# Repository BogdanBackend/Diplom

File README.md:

Автоматизований портативний комплекс виявлення та аналізу радіосигналів

---

A1:

* [Збірне креслення](pdf/A1/Assem.pdf)
* [Бокс креслення](pdf/A1/Box.pdf)
* [Електрична креслення](pdf/A1/CM5IO.pdf)
* [Експеремент плакат](pdf/A1/A1_experiment.drawio.pdf)
* [Плата плакат](pdf/A1/PCB.pdf)

A4:

* [Записка](pdf/doc.pdf)
* [Захис екрану креслення](pdf/A4/Top.pdf)
* [Захист роз'ємів креслення](pdf/A4/Cover.pdf)
* [Специфікація](pdf/A4/Специфікація.pdf)
* [Звіт плагіату](pdf/A4/Plagiarism.pdf)

---

# __[ЗМІСТ](docs/README.md)__

* [DOCx проміжковий файл розділів](docs/out/doc_dev.docx)

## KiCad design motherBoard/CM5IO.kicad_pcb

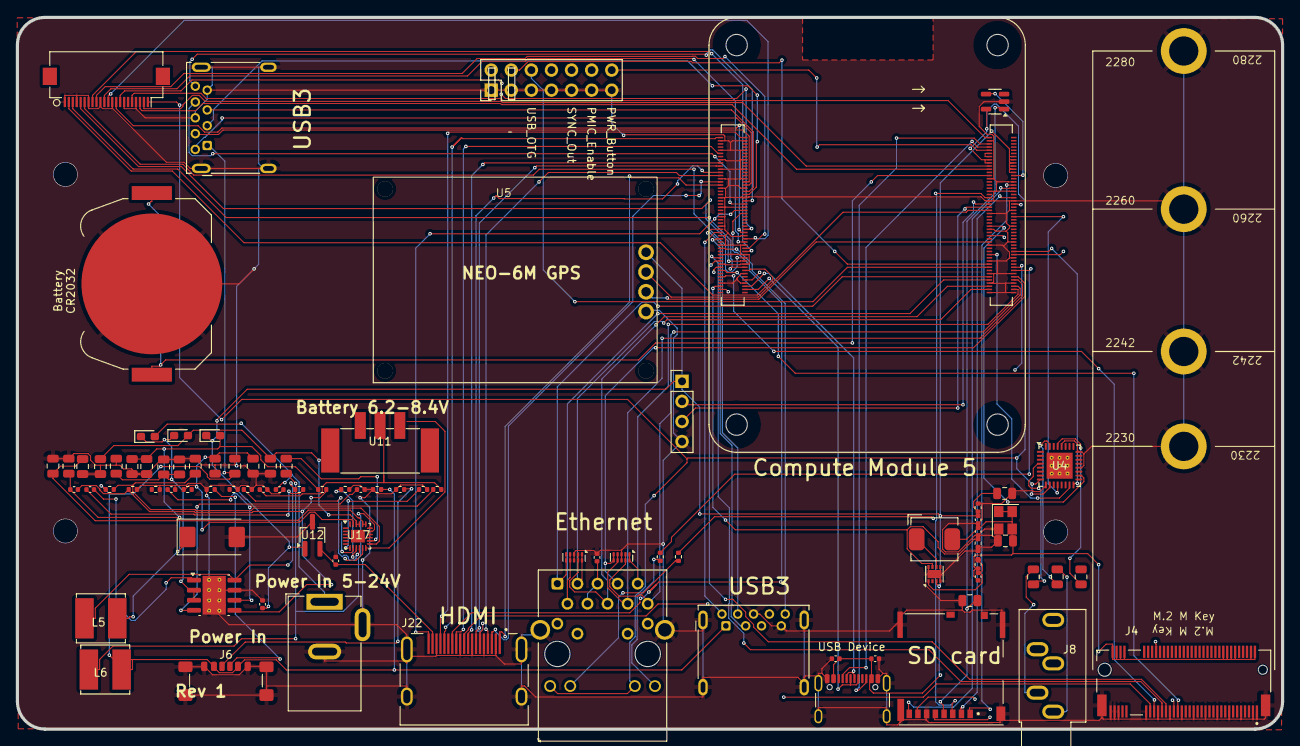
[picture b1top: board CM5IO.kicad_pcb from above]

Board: 4 copper layers, 160.0 x 90.0 mm, 88 parts (0 on the bottom side), 124 nets.

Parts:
BT1: Battery_Cell; BatteryHolder_Keystone_3034_1x20mm
C1, C9, C10, C12, C13, C18, C19, C57, C58: 100n; C_0402_1005Metric
C5, C6, C7, C8, C14, C21, C47, C49, C51, C54, C55, C56, C62, C63, C64, C65, C66, C67: 10u; C_0805_2012Metric
C11: 4.7nF; C_0402_1005Metric
C20: 100uF; CP_EIA-7343-31_Kemet-D
C34, C37, C39: 10u 35v; C_0805_2012Metric
C36: 100n 100v; C_0402_1005Metric
C59, C61: nf; C_0402_1005Metric
C60: 1.2nF; C_0402_1005Metric
D4, D5, D6: D_Zener; D_0603_1608Metric_Pad1.05x0.95mm_HandSolder
J1, J3: USB3_A; USB3_A_Molex_48393-001
J2: Conn_02x07_Odd_Even; PinHeader_2x07_P2.54mm_Vertical
J4: Bus_M.2_Socket_M; M.2 M Key socket
J5: Conn_01x22; Hirose_FH12-22S-0.5SH_1x22-1MP_P0.50mm_Horizontal
J6: USB_C; USB_C_Receptacle_GCT_USB4135-GF-A_6P_TopMnt_Horizontal
J7: Micro_SD_Card_Det; SDCARD_MOLEX_503398-1892
J8: AudioJack; Jack_3.5mm_CUI_SJ1-3535NG_Horizontal
J11: USB_C; USB_C_Receptacle_GCT_USB4105-xx-A_16P_TopMnt_Horizontal
J19: Barrel_Jack; BarrelJack_GCT_DCJ200-10-A_Horizontal
J22: 690-019-298-412; EDAC 690-019-298-412
L1: 2.2uH; L_Bourns_SRP5030CC
L5, L6: SRN6045TA-3R3Y; L_Bourns_SRN6045TA
Module1: ComputeModule5-CM5; Raspberry-Pi-5-Compute-Module
R2, R3: 470R; R_0402_1005Metric
R9, R16, R28: 2.2K 1%; R_0402_1005Metric
R10, R22, R23, R24, R30, R31: 10R; R_0402_1005Metric
R14: 100K; R_0402_1005Metric
R15: 10K 1%; R_0402_1005Metric
R25: 20K 1%; R_0402_1005Metric
R27: 12K 1%; R_0402_1005Metric
R34: 12K; R_0402_1005Metric
R35: 10K; R_0402_1005Metric
R37: 0.5K; R_0402_1005Metric
R38: 1K; R_0402_1005Metric
R39: 18K; R_0402_1005Metric
U1, U2: TPD4EUSB30; USON-10_2.5x1.0mm_P0.5mm
U3: MagJack-A70-112; TRJG0926HENL
U4: WM8960; QFN-32-1EP_5x5mm_P0.5mm_EP3.3x3.3mm_ThermalVias
U5: NEO-6M GPS
U6: Touch; PinHeader_1x04_P2.54mm_Vertical
U7: 32.768KHZ; Crystal_SMD_3225-4Pin_3.2x2.5mm
U8: AP3441SHE-7B; DFN-8-1EP_2x2mm_P0.5mm_EP1.05x1.75mm
U11: BK-18650-PC4; TerminalBlock_Phoenix_PTSM-0,5-3-2,5-V-SMD_1x03-1MP_P2.50mm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
U12: RT9742SNGV; TSOT-23_HandSoldering
U16: AP64501SP-13; SOIC-8-1EP_3.9x4.9mm_P1.27mm_EP2.95x4.9mm_Mask2.71x3.4mm_Th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
U17: IP2326; QFN-24-1EP_3x3mm_P0.4mm_EP1.75x1.6mm
U18: RT9742GGJ5; SOT-23-5

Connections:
/+1.8v: Module1.88 (+1.8v_(Output)), Module1.90 (+1.8v_(Output))
/+3.3v: J5.22, Module1.84 (+3.3v_(Output)), Module1.86 (+3.3v_(Output)), U3.15 (LEDY_A), U3.17 (LEDG_A), U4.8 (DCVDD), U4.10 (DBVDD), U18.5 (IN)
/+5v: C6.1, C9.1, C10.1, C12.1, C18.1, D4.1 (K), J11.A4 (VBUS), J11.A9 (VBUS), J11.B4 (VBUS), J11.B9 (VBUS), Module1.77 (+5v_(Input)), Module1.79 (+5v_(Input)), Module1.81 (+5v_(Input)), Module1.83 (+5v_(Input)), Module1.85 (+5v_(Input)), Module1.87 (+5v_(Input)), R9.2, U5.1 (VCC), U6.1 (VCC), U8.3 (VIN), U12.1 (IN)
/+12v: C34.1, C37.1, C39.1, D5.1 (K), D6.1 (K), U16.2 (VIN), U16.3 (EN)
/CAM_GPIO1: J5.18, Module1.100 (CAM_GPIO1)
/CC1: J11.A5 (CC1), Module1.94 (CC1)
/CC2: J11.B5 (CC2), Module1.96 (CC2)
/DPHY0_C_N: J5.8, Module1.127 (MIPI0_C_N)
/DPHY0_C_P: J5.9, Module1.129 (MIPI0_C_P)
/DPHY0_D0_N: J5.2, Module1.115 (MIPI0_D0_N)
/DPHY0_D0_P: J5.3, Module1.117 (MIPI0_D0_P)
/DPHY0_D1_N: J5.5, Module1.121 (MIPI0_D1_N)
/DPHY0_D1_P: J5.6, Module1.123 (MIPI0_D1_P)
/DPHY0_D2_N: J5.11, Module1.133 (MIPI0_D2_N)
/DPHY0_D2_P: J5.12, Module1.135 (MIPI0_D2_P)
/DPHY0_D3_N: J5.14, Module1.139 (MIPI0_D3_N)
/DPHY0_D3_P: J5.15, Module1.141 (MIPI0_D3_P)
/EEPROM_nWP: J2.4, Module1.20 (EEPROM_nWP)
/ETH_LEDG: Module1.17 (Ethernet_nLED2(3.3v)), R2.2
/ETH_LEDY: Module1.15 (Ethernet_nLED3(3.3v)), R3.2
/FB: C11.2, R15.2, R16.1, U8.1 (FB)
/GPIO2: Module1.58 (GPIO2), U6.2 (SDA)
/GPIO3: Module1.56 (GPIO3), U6.3 (SCL)
/GPIO4: Module1.54 (GPIO4), U5.2 (RX)
/GPIO5: Module1.34 (GPIO5), U5.3 (TX)
/GPIO10: Module1.44 (GPIO10), U4.18 (SDA)
/GPIO11: Module1.38 (GPIO11), U4.17 (SCL)
/GPIO18: Module1.49 (GPIO18), U4.12 (BCLK)
/GPIO19: Module1.26 (GPIO19), U4.15 (ADCLRC/GPIO)
/GPIO20: Module1.27 (GPIO20), U4.16 (ADCDAT)
/GPIO21: Module1.25 (GPIO21), U4.14 (DACDAT)
/HDMI0_CEC: J22.13 (CEC), Module1.151 (HDMI0_CEC)
/HDMI0_CK_N: J22.12 (CK-), Module1.190 (HDMI0_CLK_N)
/HDMI0_CK_P: J22.10 (CK+), Module1.188 (HDMI0_CLK_P)
/HDMI0_D0_N: J22.9 (D0-), Module1.184 (HDMI0_TX0_N)
/HDMI0_D0_P: J22.7 (D0+), Module1.182 (HDMI0_TX0_P)
/HDMI0_D1_N: J22.6 (D1-), Module1.178 (HDMI0_TX1_N)
/HDMI0_D1_P: J22.4 (D1+), Module1.176 (HDMI0_TX1_P)
/HDMI0_D2_N: J22.3 (D2-), Module1.172 (HDMI0_TX2_N)
/HDMI0_D2_P: J22.1 (D2+), Module1.170 (HDMI0_TX2_P)
/HDMI0_HOTPLUG: J22.19 (HPD/HEAC-), Module1.153 (HDMI0_HOTPLUG)
/HDMI0_SCL: J22.15 (SCL), Module1.200 (HDMI0_SCL)
/HDMI0_SDA: J22.16 (SDA), Module1.199 (HDMI0_SDA)
/HDMI_5v: C13.1, J22.18 (+5V), U12.2 (OUT)
/M2_3v3: C11.1, C14.1, C19.1, J4.2 (3.3V), J4.4 (3.3V), J4.12 (3.3V), J4.14 (3.3V), J4.16 (3.3V), J4.18 (3.3V), J4.68 (SUSCLK), J4.70 (3.3V), J4.72 (3.3V), J4.74 (3.3V), L1.2, R15.1, U7.1 (EN), U7.3 (Out), U7.4 (VDD)
/PCIE_CLK_N: J4.53 (REFCLKn), Module1.112 (PCIe_CLK_N)
/PCIE_CLK_P: J4.55 (REFCLKp), Module1.110 (PCIe_CLK_P)
/PCIE_PWR_EN: Module1.106 (PCIE_PWR_EN), R14.1, U8.7 (EN)
/PCIE_RX_N: J4.43 (PETp0), Module1.118 (PCIe_RX_N)
/PCIE_RX_P: J4.41 (PETn0), Module1.116 (PCIe_RX_P)
/PCIE_TX_N: J4.49 (PERp0), Module1.124 (PCIe_TX_N)
/PCIE_TX_P: J4.47 (PERn0), Module1.122 (PCIe_TX_P)
/PCIE_nCLKREQ: J4.52 (~CLKREQ), Module1.102 (PCIe_nCLKREQ)
/PCIE_nRST: J4.50 (~PERST), Module1.109 (PCIe_nRST)
/PCIE_nWAKE: J4.54 (~PEWAKE), Module1.104 (PCIE_nWAKE)
/PWR_BUT: J2.14, Module1.92 (PWR_BUT)
/SCL0: J5.20, Module1.80 (SCL0)
/SDA0: J5.21, Module1.82 (SDA0)
/SD_CLK: J7.5 (CLK), Module1.57 (SD_CLK)
/SD_CMD: J7.3 (CMD), Module1.62 (SD_CMD)
/SD_DAT0: J7.7 (DAT0), Module1.63 (SD_DAT0)
/SD_DAT1: J7.8 (DAT1), Module1.67 (SD_DAT1)
/SD_DAT2: J7.1 (DAT2), Module1.69 (SD_DAT2)
/SD_DAT3: J7.2 (DAT3/CD), Module1.61 (SD_DAT3)
/SD_PWR: C5.1, J7.4 (VDD), U18.1 (OUT)
/SD_PWR_ON: Module1.75 (SD_PWR_ON), U18.4 (EN)
/SYNC_OUT: J2.6, Module1.18 (Ethernet_SYNC_OUT(3.3v))
/TRD0_N: Module1.10 (Ethernet_Pair0_N), U2.4 (D2+), U2.7, U3.2 (TRD0-)
/TRD0_P: Module1.12 (Ethernet_Pair0_P), U2.5 (D2-), U2.6, U3.1 (TRD0+)
/TRD1_N: Module1.6 (Ethernet_Pair1_N), U2.2 (D1-), U2.9, U3.6 (TRD1-)
/TRD1_P: Module1.4 (Ethernet_Pair1_P), U2.1 (D1+), U2.10, U3.3 (TRD1+)
/TRD2_N: Module1.9 (Ethernet_Pair2_N), U1.4 (D2+), U1.7, U3.8 (TRD2-)
/TRD2_P: Module1.11 (Ethernet_Pair2_P), U1.5 (D2-), U1.6, U3.7 (TRD2+)
/TRD3_N: Module1.5 (Ethernet_Pair3_N), U1.2 (D1-), U1.9, U3.10 (TRD3-)
/TRD3_P: Module1.3 (Ethernet_Pair3_P), U1.1 (D1+), U1.10, U3.9 (TRD3+)
/USB2_N: J11.A6 (D+), J11.B6 (D+), Module1.103 (USB2_N)
/USB2_P: J11.A7 (D-), J11.B7 (D-), Module1.105 (USB2_P)
/USB3-0-D_N: J3.2 (D-), Module1.136 (USB3-0-D_N)
/USB3-0-D_P: J3.3 (D+), Module1.134 (USB3-0-D_P)
/USB3-0-RX_N: J3.6 (SSRX+), Module1.128 (USB3-0-RX_N)
/USB3-0-RX_P: J3.5 (SSRX-), Module1.130 (USB3-0-RX_P)
/USB3-0-TX_N: J3.9 (SSTX+), Module1.140 (USB3-0-TX_N)
/USB3-0-TX_P: J3.8 (SSTX-), Module1.142 (USB3-0-TX_P)
/USB3-1-D_N: J1.3 (D+), Module1.165 (USB3-1-D_N)
/USB3-1-D_P: J1.2 (D-), Module1.163 (USB3-1-D_P)
/USB3-1-RX_N: J1.6 (SSRX+), Module1.157 (USB3-1-RX_N)
/USB3-1-RX_P: J1.5 (SSRX-), Module1.159 (USB3-1-RX_P)
/USB3-1-TX_N: J1.9 (SSTX+), Module1.169 (USB3-1-TX_N)
/USB3-1-TX_P: J1.8 (SSTX-), Module1.171 (USB3-1-TX_P)
/VBAT: BT1.1 (+), Module1.76 (VBAT)
/VBUS: J1.1 (VBUS), J3.1 (VBUS)
/Vbus: C55.1, J6.A9 (VBUS), J6.B9 (VBUS), L6.2, R22.1, R23.2
GND: BT1.2 (-), C1.2, C5.2, C6.2, C9.2, C10.2, C12.2, C13.2, C14.2, C18.2, C19.2, C20.2, C34.2, C36.2, C37.2, C39.2, C47.2, C49.2, C51.2, C55.2, C56.2, C58.2, C59.2, C60.2, C62.2, C63.2, C64.2, C65.2, C66.1, C67.1, J1.4 (GND), J1.7 (DRAIN), J1.10 (SHIELD), J2.1, J2.3, J2.5, J2.7, J2.9, J2.11, J2.13, J3.4 (GND), J3.7 (DRAIN), J3.10 (SHIELD), J4.1 (GND), J4.3 (GND), J4.9 (GND), J4.15 (GND), J4.21 (GND), J4.27 (GND), J4.33 (GND), J4.39 (GND), J4.45 (GND), J4.51 (GND), J4.57 (GND), J4.71 (GND), J4.73 (GND), J4.75 (GND), J4.M1 (GND2230), J4.M2 (GND2242), J4.M3 (GND2260), J4.M4 (GND2280), J4.S1, J4.S2, J5.1, J5.4, J5.7, J5.10, J5.13, J5.16, J5.19, J6.A12 (GND), J6.B12 (GND), J6.S1 (SHIELD), J7.6 (VSS), J7.11 (SHIELD), J11.A1 (GND), J11.A12 (GND), J11.B1 (GND), J11.B12 (GND), J11.S1 (SHIELD), J19.2, J19.3, J22.2 (D2S), J22.5 (D1S), J22.8 (D0S), J22.11 (CKS), J22.17 (GND), J22.SH1 (SH), J22.SH2 (SH), J22.SH3 (SH), J22.SH4 (SH), Module1.1 (GND), Module1.2 (GND), Module1.7 (GND), Module1.8 (GND), Module1.13 (GND), Module1.14 (GND), Module1.22 (GND), Module1.23 (GND), Module1.32 (GND), Module1.33 (GND), Module1.42 (GND), Module1.43 (GND), Module1.52 (GND), Module1.53 (GND), Module1.59 (GND), Module1.60 (GND), Module1.65 (GND), Module1.66 (GND), Module1.71 (GND), Module1.74 (GND), Module1.98 (GND), Module1.107 (GND), Module1.108 (GND), Module1.113 (GND), Module1.114 (GND), Module1.119 (GND), Module1.120 (GND), Module1.125 (GND), Module1.126 (GND), Module1.131 (GND), Module1.132 (GND), Module1.137 (GND), Module1.138 (GND), Module1.144 (GND), Module1.150 (GND), Module1.155 (GND), Module1.156 (GND), Module1.161 (GND), Module1.162 (GND), Module1.167 (GND), Module1.168 (GND), Module1.173 (GND), Module1.174 (GND), Module1.179 (GND), Module1.180 (GND), Module1.185 (GND), Module1.186 (GND), Module1.191 (GND), Module1.192 (GND), Module1.197 (GND), Module1.198 (GND), R9.1, R14.2, R16.2, R23.1, R28.2, R30.1, R31.1, R34.2, R35.2, R37.2, R38.2, R39.2, U1.3 (GND), U1.8 (GND), U2.3 (GND), U2.8 (GND), U3.19 (SHIELD), U3.20 (SHIELD), U4.9 (DGND), U4.20 (SPKGND2), U4.24 (SPKGND1), U4.28 (AGND), U5.4 (GND), U6.4 (GND), U7.2 (GND), U8.4 (PGND), U8.8 (SGND), U8.9 (PAD), U12.3 (GND), U16.7 (GND), U16.9 (EP), U17.18 (PGND), U17.24 (VBAT_GND), U18.2 (GND)
unnamed: C1.1, U3.4 (CT), U3.5 (CT)
unnamed: C7.2, J8.T
unnamed: C8.2, J8.S
unnamed: C54.1, L6.1, U17.15 (LX), U17.16 (LX), U17.17 (LX)
unnamed: C57.1, R10.2
unnamed: C60.1, R25.2
unnamed: C62.1, C63.1, U17.19 (VSYS), U17.20 (VSYS)
unnamed: C20.1, C47.1, C49.1, C51.1, C61.1, D4.2 (A), L5.2, R27.1
unnamed: C64.1, C65.1, D5.2 (A), U17.21 (VOUT), U17.22 (VOUT)
unnamed: C36.1, D6.2 (A), J19.1
unnamed: J6.A5 (CC1), R30.2
unnamed: J6.B5 (CC2), R31.2
unnamed: R3.1, U3.18 (LEDG_K)
unnamed: R2.1, U3.16 (LEDY_K)
unnamed: C8.1, U4.31 (HEADPHONE_L)
unnamed: C21.1, U4.29 (HEADPHONE_R)
unnamed: C7.1, U4.4 (LINPUT1)
unnamed: L1.1, U8.6 (LX)
unnamed: C57.2, U16.1 (BST)
unnamed: C59.1, R25.1, U16.6 (COMP)
unnamed: C61.2, R27.2, R28.1, U16.5 (FB)
unnamed: C58.1, U16.4 (SS)
unnamed: L5.1, R10.1, U16.8 (SW)
unnamed: C54.2, U17.14 (BST)
unnamed: R39.1, U17.11 (ISET)
unnamed: R34.1, U17.10 (NC)
unnamed: R38.1, U17.7 (TIME_SET)
unnamed: C66.2, C67.2, R24.1, U17.23 (VBATM)
unnamed: C56.1, R22.2, U17.13 (VIN)
unnamed: R35.1, U17.9 (VIN_OVSET)
unnamed: R37.1, U17.8 (VIN_UVSET)

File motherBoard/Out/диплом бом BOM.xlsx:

| Позиція | Позначення | Найменування | Кількість | Примітки |  |  |  | Примітка
 |  |  | Конденсатори
 | C1, C9, C10, C12, C13, C18, C19, C57, C58 |  | Конденсатор керамічний 100n, типорозмір: 0402, ISO 60384-1 / ДСТУ Б В.2.7-245:2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 | 9 |  |  | Конденсатор керамічний 100n | ISO 60384-1 / ДСТУ Б В.2.7-245:2010 | типорозмір: 0402
 | C5-8, C14, C21, C47, C49, C51, C54-56, C62-67 |  | Конденсатор керамічний 10u, типорозмір: 0805, ISO 60384-1 / ДСТУ Б В.2.7-245:20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 | 18 |  |  | Конденсатор керамічний 10u | ISO 60384-1 / ДСТУ Б В.2.7-245:2010 | типорозмір: 0805
 | C11 |  | Конденсатор керамічний 4.7nF, типорозмір: 0402, ISO 60384-1 / ДСТУ Б В.2.7-245: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 | 1 |  |  | Конденсатор керамічний 4.7nF | ISO 60384-1 / ДСТУ Б В.2.7-245:2010 | типорозмір: 0402
 | C20 |  | Конденсатор танталовий 100uF, типорозмір: EIA-7343-31, ISO 60384-3 | 1 |  |  | Конденсатор танталовий 100uF | ISO 60384-3 | типорозмір: EIA-7343-31
 | C34, C37, C39 |  | Конденсатор керамічний 10u 35V, типорозмір: 0805, ISO 60384-1 / ДСТУ Б В.2.7-24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 | 3 |  |  | Конденсатор керамічний 10u 35V | ISO 60384-1 / ДСТУ Б В.2.7-245:2010 | типорозмір: 0805
 | C36 |  | Конденсатор керамічний 100n 100V, типорозмір: 0402, ISO 60384-1 / ДСТУ Б В.2.7-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 | 1 |  |  | Конденсатор керамічний 100n 100V | ISO 60384-1 / ДСТУ Б В.2.7-245:2010 | типорозмір: 0402
 | C59, C61 |  | Конденсатор керамічний (nf), типорозмір: 0402, ISO 60384-1 / ДСТУ Б В.2.7-245:2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 | 2 |  |  | Конденсатор керамічний (nf) | ISO 60384-1 / ДСТУ Б В.2.7-245:2010 | типорозмір: 0402
 | C60 |  | Конденсатор керамічний 1.2nF, типорозмір: 0402, ISO 60384-1 / ДСТУ Б В.2.7-245: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 | 1 |  |  | Конденсатор керамічний 1.2nF | ISO 60384-1 / ДСТУ Б В.2.7-245:2010 | типорозмір: 0402
 | D4-6 |  | Діод Зенера (D_Zener), типорозмір: 0603, ДСТУ 2449-94 / ISO 19077 | 3 |  |  | Діод Зенера (D_Zener) | ДСТУ 2449-94 / ISO 19077 | типорозмір: 0603
 |  |  | Роз'єми
 | J1, J3 |  | Роз'єм USB3_A, Molex_48393-001, ISO/IEC 14472 | 2 |  |  | Роз'єм USB3_A | ISO/IEC 14472 | Molex_48393-001
 | BT1 |  | Елемент живлення, Тримач: Keystone_3034_1x20mm, ДСТУ EN 61204:2016 / ISO 61204 | 1 |  |  | Елемент живлення | ДСТУ EN 61204:2016 / ISO 61204 | Тримач: Keystone_3034_1x20mm
 | J2 |  | З'єднувач штирьовий (Conn_02x07_Odd_Even), PinHeader_2x07_P2.54mm_Vertical, ДСТ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 | 1 |  |  | З'єднувач штирьовий (Conn_02x07_Odd_Even) | ДСТУ IEC 603-7/ ISO 14472 | PinHeader_2x07_P2.54mm_Vertical
 | J4 |  | Роз'єм Bus_M.2_Socket_M, ISO/IEC 14472 | 1 |  |  | Роз'єм Bus_M.2_Socket_M | ISO/IEC 14472 | -
 | J5 |  | З'єднувач гнучкий (Conn_01x22_Female), Hirose_FH12-22S-0.5SH, ДСТУ EN 12094-8 /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 | 1 |  |  | З'єднувач гнучкий (Conn_01x22_Female) | ДСТУ EN 12094-8 / ISO 14472 | Hirose_FH12-22S-0.5SH
 | J6 |  | Роз'єм USB-C (USB_C_Receptacle_USB2.0_14P), GCT_USB4135-GF-A, ISO/IEC 14472 | 1 |  |  | Роз'єм USB-C (USB_C_Receptacle_USB2.0_14P) | ISO/IEC 14472 | GCT_USB4135-GF-A
 | J7 |  | Роз'єм Micro_SD_Card_Det, MOLEX_503398-1892, ISO/IEC 14472 | 1 |  |  | Роз'єм Micro_SD_Card_Det | ISO/IEC 14472 | MOLEX_503398-1892
 | J8 |  | Аудіороз'єм (AudioJack4), CUI_SJ1-3535NG, ISO/IEC 29193 / ISO 14472 | 1 |  |  | Аудіороз'єм (AudioJack4) | ISO/IEC 29193 / ISO 14472 | CUI_SJ1-3535NG
 | J11 |  | Роз'єм USB-C (USB_C_Receptacle_USB2.0), GCT_USB4105-xx-A, ISO/IEC 14472 | 1 |  |  | Роз'єм USB-C (USB_C_Receptacle_USB2.0) | ISO/IEC 14472 | GCT_USB4105-xx-A
 | J19 |  | Роз'єм живлення (Barrel_Jack), GCT_DCJ200-10-A, ISO/IEC 14472 | 1 |  |  | Роз'єм живлення (Barrel_Jack) | ISO/IEC 14472 | GCT_DCJ200-10-A
 | J22 |  | З'єднувач (690-019-298-412), EDAC 690-019-298-412, ISO/IEC 14472 | 1 |  |  | З'єднувач (690-019-298-412) | ISO/IEC 14472 | EDAC 690-019-298-412
 |  |  | Ідуктивності
 | L1 |  | Індуктивність 2.2uH, Bourns_SRP5030CC, ДСТУ EN 60310:2022 / ISO 60310 | 1 |  |  | Індуктивність 2.2uH | ДСТУ EN 60310:2022 / ISO 60310 | Bourns_SRP5030CC
 | L5, L6 |  | Індуктивність SRN6045TA-3R3Y, Bourns_SRN6045TA, ДСТУ EN 60310:2022 / ISO 60310 | 2 |  |  | Індуктивність SRN6045TA-3R3Y | ДСТУ EN 60310:2022 / ISO 60310 | Bourns_SRN6045TA
 |  |  | Резистори
 | R2, R3 |  | Резистор 470R, типорозмір: 0402, ДСТУ 7953:2015 / ISO 60115 | 2 |  |  | Резистор 470R | ДСТУ 7953:2015 / ISO 60115 | типорозмір: 0402
 | R9, R16, R28 |  | Резистор 2.2K 1%, типорозмір: 0402, ДСТУ 7953:2015 / ISO 60115 | 3 |  |  | Резистор 2.2K 1% | ДСТУ 7953:2015 / ISO 60115 | типорозмір: 0402
 | R10, R22, R23, R24, R30, R31 |  | Резистор 10R, типорозмір: 0402, ДСТУ 7953:2015 / ISO 60115 | 6 |  |  | Резистор 10R | ДСТУ 7953:2015 / ISO 60115 | типорозмір: 0402
 | R14 |  | Резистор 100K, типорозмір: 0402, ДСТУ 7953:2015 / ISO 60115 | 1 |  |  | Резистор 100K | ДСТУ 7953:2015 / ISO 60115 | типорозмір: 0402
 | R15 |  | Резистор 10K 1%, типорозмір: 0402, ДСТУ 7953:2015 / ISO 60115 | 1 |  |  | Резистор 10K 1% | ДСТУ 7953:2015 / ISO 60115 | типорозмір: 0402
 | R25 |  | Резистор 20K 1%, типорозмір: 0402, ДСТУ 7953:2015 / ISO 60115 | 1 |  |  | Резистор 20K 1% | ДСТУ 7953:2015 / ISO 60115 | типорозмір: 0402
 | R27 |  | Резистор 12K 1%, типорозмір: 0402, ДСТУ 7953:2015 / ISO 60115 | 1 |  |  | Резистор 12K 1% | ДСТУ 7953:2015 / ISO 60115 | типорозмір: 0402
 | R34 |  | Резистор 12K, типорозмір: 0402, ДСТУ 7953:2015 / ISO 60115 | 1 |  |  | Резистор 12K | ДСТУ 7953:2015 / ISO 60115 | типорозмір: 0402
 | R35 |  | Резистор 10K, типорозмір: 0402, ДСТУ 7953:2015 / ISO 60115 | 1 |  |  | Резистор 10K | ДСТУ 7953:2015 / ISO 60115 | типорозмір: 0402
 | R37 |  | Резистор 0.5K, типорозмір: 0402, ДСТУ 7953:2015 / ISO 60115 | 1 |  |  | Резистор 0.5K | ДСТУ 7953:2015 / ISO 60115 | типорозмір: 0402
 | R38 |  | Резистор 1K, типорозмір: 0402, ДСТУ 7953:2015 / ISO 60115 | 1 |  |  | Резистор 1K | ДСТУ 7953:2015 / ISO 60115 | типорозмір: 0402
 | R39 |  | Резистор 18K, типорозмір: 0402, ДСТУ 7953:2015 / ISO 60115 | 1 |  |  | Резистор 18K | ДСТУ 7953:2015 / ISO 60115 | типорозмір: 0402
 |  |  | Модулі:
 | U1, U2 |  | Мікросхема TPD4EUSB30, корпус: USON-10_2.5x1.0mm_P0.5mm, ISO/IEC 14472 | 2 |  |  | Мікросхема TPD4EUSB30 | ISO/IEC 14472 | корпус: USON-10_2.5x1.0mm_P0.5mm
 | U3 |  | MagJack-A70-112-331N126, TRJG0926HENL, ISO/IEC 14472 | 1 |  |  | MagJack-A70-112-331N126 | ISO/IEC 14472 | TRJG0926HENL
 | U4 |  | Мікросхема WM8960, корпус: QFN-32-1EP_5x5mm_P0.5mm, ISO/IEC 14472 | 1 |  |  | Мікросхема WM8960 | ISO/IEC 14472 | корпус: QFN-32-1EP_5x5mm_P0.5mm
 | U5 |  | Модуль GPS NEO-6M, ДСТУ EN ISO 1101:2018 / ISO 19133 | 1 |  |  | Модуль GPS NEO-6M | ДСТУ EN ISO 1101:2018 / ISO 19133 | -
 | U6 |  | Модуль GPS NEO-6M , PinHeader_1x04_P2.54mm_Vertical, ДСТУ EN ISO 1101:2018 / IS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 | 1 |  |  | Модуль GPS NEO-6M | ДСТУ EN ISO 1101:2018 / ISO 19133 | PinHeader_1x04_P2.54mm_Vertical
 | U7 |  | Кварцовий резонатор 32.768KHZ, типорозмір: 3225-4Pin_3.2x2.5mm, ДСТУ 3113-95 / 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 | 1 |  |  | Кварцовий резонатор 32.768KHZ | ДСТУ 3113-95 / ISO 12046 | типорозмір: 3225-4Pin_3.2x2.5mm
 | U8 |  | Мікросхема AP3441SHE-7B, корпус: DFN-8-1EP_2x2mm_P0.5mm, ISO/IEC 14472 | 1 |  |  | Мікросхема AP3441SHE-7B | ISO/IEC 14472 | корпус: DFN-8-1EP_2x2mm_P0.5mm
 | U10, U11 |  | Модуль живлення BK-18650-PC4, ДСТУ EN 61204:2016/ ISO 61204 | 1 |  |  | Модуль живлення BK-18650-PC4 | ДСТУ EN 61204:2016/ ISO 61204
 | U12 |  | Мікросхема RT9742SNGV, корпус: TSOT-23, ISO/IEC 14472 | 1 |  |  | Мікросхема RT9742SNGV | ISO/IEC 14472 | корпус: TSOT-23
 | U16 |  | Мікросхема AP64501SP-13, корпус: SOIC-8-1EP, ISO/IEC 14472 | 1 |  |  | Мікросхема AP64501SP-13 | ISO/IEC 14472 | корпус: SOIC-8-1EP
 | U17 |  | Мікросхема IP2326, корпус: QFN-24-1EP_3x3mm_P0.4mm, ISO/IEC 14472 | 1 |  |  | Мікросхема IP2326 | ISO/IEC 14472 | корпус: QFN-24-1EP_3x3mm_P0.4mm
 | U18 |  | Мікросхема RT9742GGJ5, корпус: SOT-23-5, ISO/IEC 14472 | 1 |  |  | Мікросхема RT9742GGJ5 | ISO/IEC 14472 | корпус: SOT-23-5
 | Module1 |  | Обчислювальний модуль RPi CM5, ДСТУ 2229-93 / ISO/IEC 18000 | 1 |  |  | Обчислювальний модуль RPi CM5 | ДСТУ 2229-93 / ISO/IEC 18000

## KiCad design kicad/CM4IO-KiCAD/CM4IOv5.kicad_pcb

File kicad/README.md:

материнська плата 

[Завантажити проєкт KiCad](https://download-directory.github.io/?url=https://github.com/Bogd-an/Diplom/tree/main/kicad/CM4IO-KiCAD)

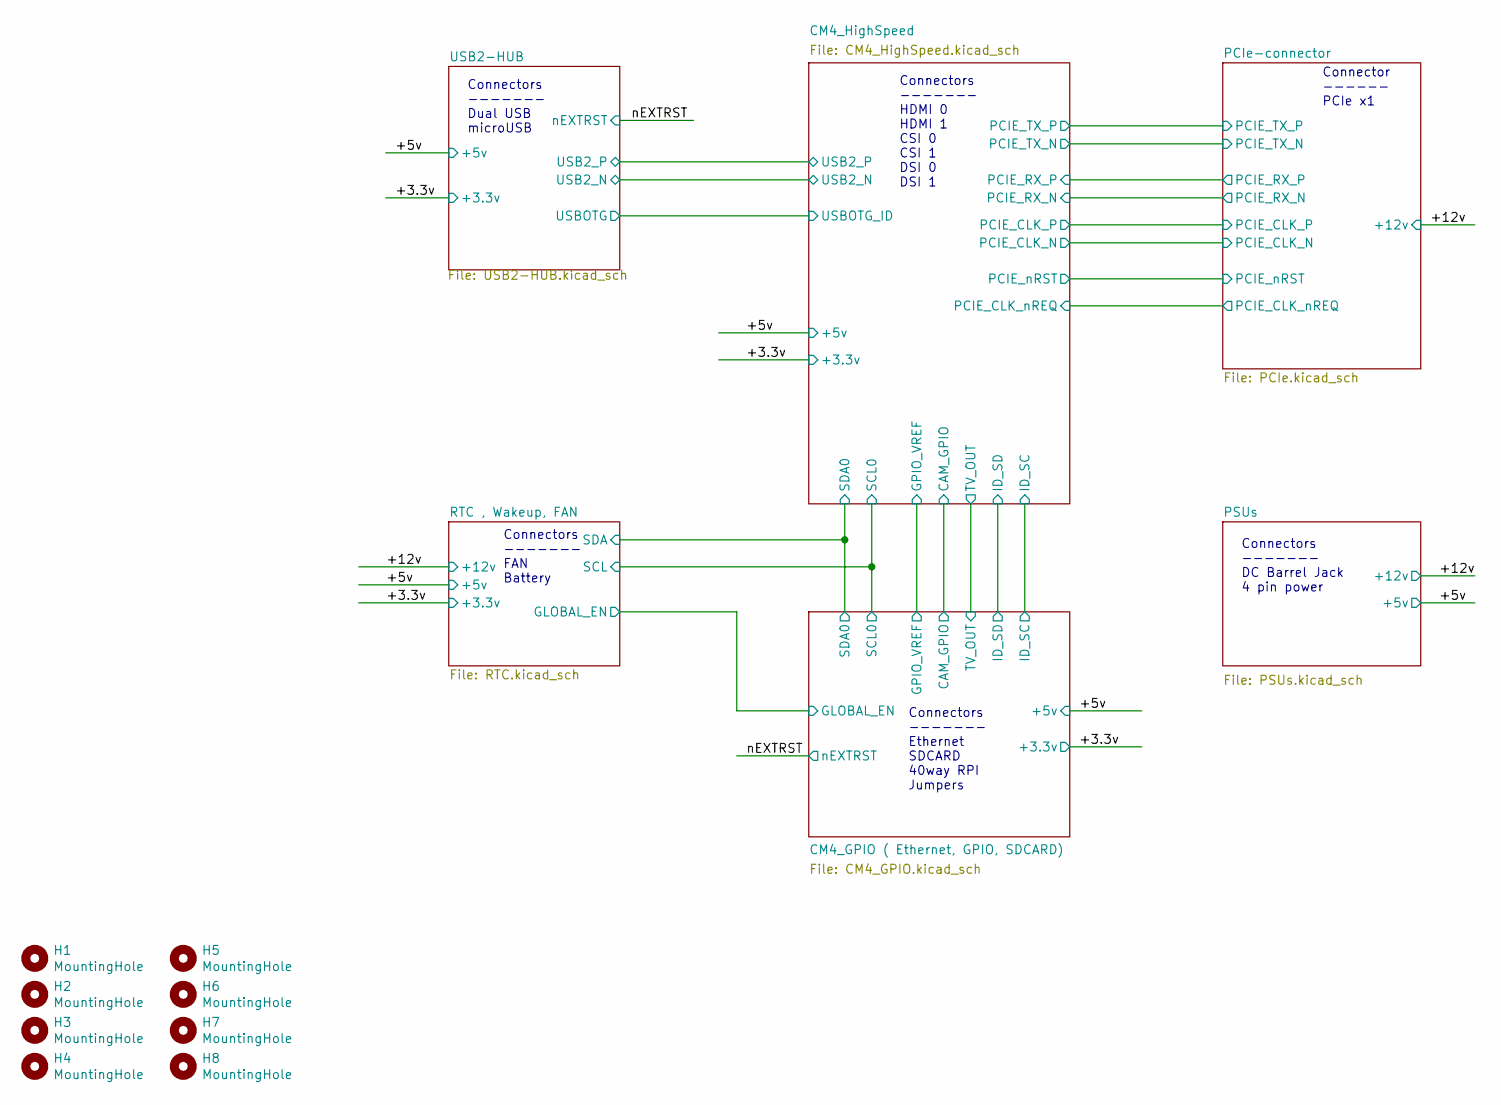
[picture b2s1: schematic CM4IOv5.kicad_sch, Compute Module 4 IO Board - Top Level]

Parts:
H1, H2, H3, H4, H5, H6, H7, H8: MountingHole; MountingHole_2.7mm_M2.5; Part Description M2.5 mounting hole

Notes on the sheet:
Connectors ------- FAN Battery
Connector ------ PCIe x1
Connectors ------- DC Barrel Jack 4 pin power
Connectors ------- Dual USB microUSB
Connectors ------- Ethernet SDCARD 40way RPI Jumpers
Connectors ------- HDMI 0 HDMI 1 CSI 0 CSI 1 DSI 0 DSI 1

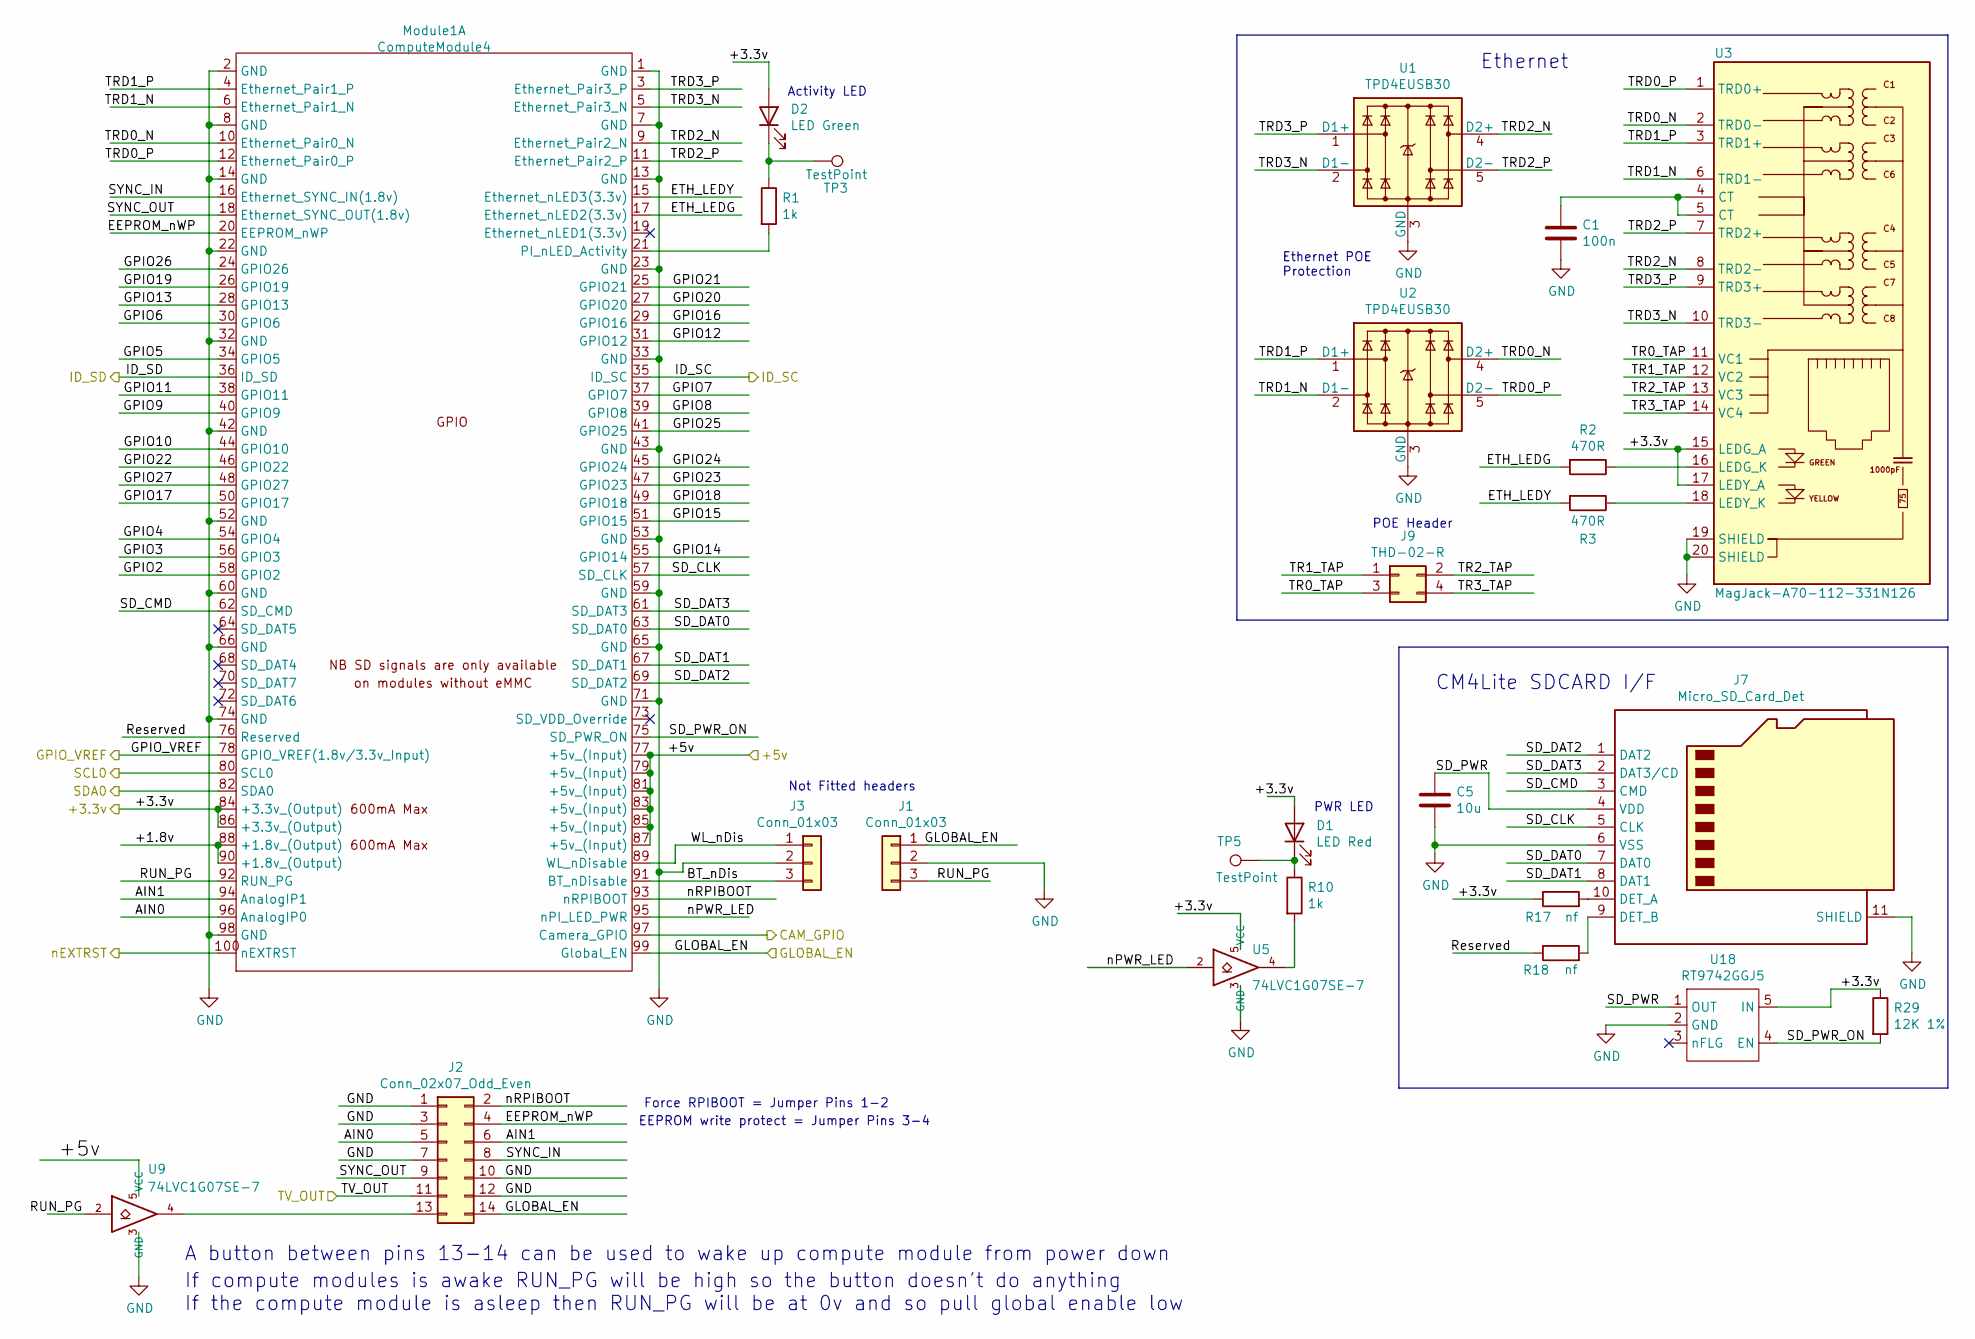
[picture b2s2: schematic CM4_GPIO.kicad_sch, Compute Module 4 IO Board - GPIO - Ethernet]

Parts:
C1: 100n; C_0402_1005Metric; Part Description 0.1uF 10% 16V Ceramic Capacitor X7R 040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
C5: 10u; C_0805_2012Metric; Part Description 10uF 10% 10V Ceramic Capacitor X7R 0805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
D1: LED Red; LED_0603_1608Metric; Part Description Red 620nm LED Indication - Discrete 2.2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
D2: LED Green; LED_0603_1608Metric; Part Description Green 572nm LED Indication - Discrete 2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
J1, J3: Conn_01x03; PinHeader_1x03_P2.54mm_Vertical; Part Description 3pin 0.1" connector
J2: Conn_02x07_Odd_Even; PinHeader_2x07_P2.54mm_Vertical; Part Description PinHeader_2x07_P2.54mm_Vertical
J7: Micro_SD_Card_Det; SDCARD_MOLEX_503398-1892; Part Description 9 (8 + 1) Position Card Connector micro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
J9: THD-02-R; PinHeader_2x02_P2.54mm_Vertical; Part Description PinHeader_2x02_P2.54mm_Vertical
Module1: ComputeModule4; Raspberry-Pi-4-Compute-Module; Part Description 100 Position Connector Receptacle, Cent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
R1, R10: 1k; R_0402_1005Metric; Part Description Resistor 1K M1005 1% 63mW
R2, R3: 470R; R_0402_1005Metric; Part Description Resistor 470R M1005 1% 63mW
R17, R18: nf; R_0402_1005Metric; Part Description Resistor 1K M1005 1% 63mW
R29: 12K 1%; R_0402_1005Metric; Part Description Resistor 12K M1005 1% 63mW
TP3, TP5: TestPoint; TestPoint_Pad_2.0x2.0mm
U1, U2: TPD4EUSB30; USON-10_2.5x1.0mm_P0.5mm; Part Description Quad TVS diode for high speed signals (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
U3: MagJack-A70-112-331N126; TRJG0926HENL; Part Description Gigabit Ethernet Magjack
U5, U9: 74LVC1G07SE-7; SOT-353_SC-70-5; Part Description Buffer, Non-Inverting 1 Element 1 Bit p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
U18: RT9742GGJ5; SOT-23-5; Part Description Power Switch/Driver 1:1 N-Channel 1A TS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

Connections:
/+3.3v: D1.2 (A), D2.2 (A), Module1.84 (+3.3v_(Output)), Module1.86 (+3.3v_(Output)), R17.1, R29.1, U3.15 (LEDG_A), U3.17 (LEDY_A), U5.5 (VCC), U18.5 (IN); also elsewhere on the board
/+5v: Module1.77 (+5v_(Input)), Module1.79 (+5v_(Input)), Module1.81 (+5v_(Input)), Module1.83 (+5v_(Input)), Module1.85 (+5v_(Input)), Module1.87 (+5v_(Input)), U9.5 (VCC); also elsewhere on the board
/CM4_GPIO ( Ethernet, GPIO, SDCARD)/+1.8v: Module1.88 (+1.8v_(Output)), Module1.90 (+1.8v_(Output))
/CM4_GPIO ( Ethernet, GPIO, SDCARD)/AIN0: J2.5, Module1.96 (AnalogIP0)
/CM4_GPIO ( Ethernet, GPIO, SDCARD)/AIN1: J2.6, Module1.94 (AnalogIP1)
/CM4_GPIO ( Ethernet, GPIO, SDCARD)/BT_nDis: J3.3, Module1.91 (BT_nDisable)
/CM4_GPIO ( Ethernet, GPIO, SDCARD)/CAM_GPIO: Module1.97 (Camera_GPIO)
/CM4_GPIO ( Ethernet, GPIO, SDCARD)/EEPROM_nWP: J2.4, Module1.20 (EEPROM_nWP)
/CM4_GPIO ( Ethernet, GPIO, SDCARD)/ETH_LEDG: Module1.17 (Ethernet_nLED2(3.3v)), R2.2
/CM4_GPIO ( Ethernet, GPIO, SDCARD)/ETH_LEDY: Module1.15 (Ethernet_nLED3(3.3v)), R3.2
/CM4_GPIO ( Ethernet, GPIO, SDCARD)/GLOBAL_EN: J1.1, J2.14, Module1.99 (Global_EN); also elsewhere on the board
/CM4_GPIO ( Ethernet, GPIO, SDCARD)/GPIO2: Module1.58 (GPIO2)
/CM4_GPIO ( Ethernet, GPIO, SDCARD)/GPIO3: Module1.56 (GPIO3)
/CM4_GPIO ( Ethernet, GPIO, SDCARD)/GPIO4: Module1.54 (GPIO4)
/CM4_GPIO ( Ethernet, GPIO, SDCARD)/GPIO5: Module1.34 (GPIO5)
/CM4_GPIO ( Ethernet, GPIO, SDCARD)/GPIO6: Module1.30 (GPIO6)
/CM4_GPIO ( Ethernet, GPIO, SDCARD)/GPIO7: Module1.37 (GPIO7)
/CM4_GPIO ( Ethernet, GPIO, SDCARD)/GPIO8: Module1.39 (GPIO8)
/CM4_GPIO ( Ethernet, GPIO, SDCARD)/GPIO9: Module1.40 (GPIO9)
/CM4_GPIO ( Ethernet, GPIO, SDCARD)/GPIO10: Module1.44 (GPIO10)
/CM4_GPIO ( Ethernet, GPIO, SDCARD)/GPIO11: Module1.38 (GPIO11)
/CM4_GPIO ( Ethernet, GPIO, SDCARD)/GPIO12: Module1.31 (GPIO12)
/CM4_GPIO ( Ethernet, GPIO, SDCARD)/GPIO13: Module1.28 (GPIO13)
/CM4_GPIO ( Ethernet, GPIO, SDCARD)/GPIO14: Module1.55 (GPIO14)
/CM4_GPIO ( Ethernet, GPIO, SDCARD)/GPIO15: Module1.51 (GPIO15)
/CM4_GPIO ( Ethernet, GPIO, SDCARD)/GPIO16: Module1.29 (GPIO16)
/CM4_GPIO ( Ethernet, GPIO, SDCARD)/GPIO17: Module1.50 (GPIO17)
/CM4_GPIO ( Ethernet, GPIO, SDCARD)/GPIO18: Module1.49 (GPIO18)
/CM4_GPIO ( Ethernet, GPIO, SDCARD)/GPIO19: Module1.26 (GPIO19)
/CM4_GPIO ( Ethernet, GPIO, SDCARD)/GPIO20: Module1.27 (GPIO20)
/CM4_GPIO ( Ethernet, GPIO, SDCARD)/GPIO21: Module1.25 (GPIO21)
/CM4_GPIO ( Ethernet, GPIO, SDCARD)/GPIO22: Module1.46 (GPIO22)
/CM4_GPIO ( Ethernet, GPIO, SDCARD)/GPIO23: Module1.47 (GPIO23)
/CM4_GPIO ( Ethernet, GPIO, SDCARD)/GPIO24: Module1.45 (GPIO24)
/CM4_GPIO ( Ethernet, GPIO, SDCARD)/GPIO25: Module1.41 (GPIO25)
/CM4_GPIO ( Ethernet, GPIO, SDCARD)/GPIO26: Module1.24 (GPIO26)
/CM4_GPIO ( Ethernet, GPIO, SDCARD)/GPIO27: Module1.48 (GPIO27)
/CM4_GPIO ( Ethernet, GPIO, SDCARD)/GPIO_VREF: Module1.78 (GPIO_VREF(1.8v/3.3v_Input))
/CM4_GPIO ( Ethernet, GPIO, SDCARD)/ID_SC: Module1.35 (ID_SC)
/CM4_GPIO ( Ethernet, GPIO, SDCARD)/ID_SD: Module1.36 (ID_SD)
/CM4_GPIO ( Ethernet, GPIO, SDCARD)/RUN_PG: J1.3, Module1.92 (RUN_PG), U9.2
/CM4_GPIO ( Ethernet, GPIO, SDCARD)/Reserved: Module1.76 (Reserved), R18.1
/CM4_GPIO ( Ethernet, GPIO, SDCARD)/SD_CLK: J7.5 (CLK), Module1.57 (SD_CLK)
/CM4_GPIO ( Ethernet, GPIO, SDCARD)/SD_CMD: J7.3 (CMD), Module1.62 (SD_CMD)
/CM4_GPIO ( Ethernet, GPIO, SDCARD)/SD_DAT0: J7.7 (DAT0), Module1.63 (SD_DAT0)
/CM4_GPIO ( Ethernet, GPIO, SDCARD)/SD_DAT1: J7.8 (DAT1), Module1.67 (SD_DAT1)
/CM4_GPIO ( Ethernet, GPIO, SDCARD)/SD_DAT2: J7.1 (DAT2), Module1.69 (SD_DAT2)
/CM4_GPIO ( Ethernet, GPIO, SDCARD)/SD_DAT3: J7.2 (DAT3/CD), Module1.61 (SD_DAT3)
/CM4_GPIO ( Ethernet, GPIO, SDCARD)/SD_PWR: C5.1, J7.4 (VDD), U18.1 (OUT)
/CM4_GPIO ( Ethernet, GPIO, SDCARD)/SD_PWR_ON: Module1.75 (SD_PWR_ON), R29.2, U18.4 (EN)
/CM4_GPIO ( Ethernet, GPIO, SDCARD)/SYNC_IN: J2.8, Module1.16 (Ethernet_SYNC_IN(1.8v))
/CM4_GPIO ( Ethernet, GPIO, SDCARD)/SYNC_OUT: J2.9, Module1.18 (Ethernet_SYNC_OUT(1.8v))
/CM4_GPIO ( Ethernet, GPIO, SDCARD)/TR0_TAP: J9.3, U3.11 (VC1)
/CM4_GPIO ( Ethernet, GPIO, SDCARD)/TR1_TAP: J9.1, U3.12 (VC2)
/CM4_GPIO ( Ethernet, GPIO, SDCARD)/TR2_TAP: J9.2, U3.13 (VC3)
/CM4_GPIO ( Ethernet, GPIO, SDCARD)/TR3_TAP: J9.4, U3.14 (VC4)
/CM4_GPIO ( Ethernet, GPIO, SDCARD)/TRD0_N: Module1.10 (Ethernet_Pair0_N), U2.4 (D2+), U2.7, U3.2 (TRD0-)
/CM4_GPIO ( Ethernet, GPIO, SDCARD)/TRD0_P: Module1.12 (Ethernet_Pair0_P), U2.5 (D2-), U2.6, U3.1 (TRD0+)
/CM4_GPIO ( Ethernet, GPIO, SDCARD)/TRD1_N: Module1.6 (Ethernet_Pair1_N), U2.2 (D1-), U2.9, U3.6 (TRD1-)
/CM4_GPIO ( Ethernet, GPIO, SDCARD)/TRD1_P: Module1.4 (Ethernet_Pair1_P), U2.1 (D1+), U2.10, U3.3 (TRD1+)
/CM4_GPIO ( Ethernet, GPIO, SDCARD)/TRD2_N: Module1.9 (Ethernet_Pair2_N), U1.4 (D2+), U1.7, U3.8 (TRD2-)
/CM4_GPIO ( Ethernet, GPIO, SDCARD)/TRD2_P: Module1.11 (Ethernet_Pair2_P), U1.5 (D2-), U1.6, U3.7 (TRD2+)
/CM4_GPIO ( Ethernet, GPIO, SDCARD)/TRD3_N: Module1.5 (Ethernet_Pair3_N), U1.2 (D1-), U1.9, U3.10 (TRD3-)
/CM4_GPIO ( Ethernet, GPIO, SDCARD)/TRD3_P: Module1.3 (Ethernet_Pair3_P), U1.1 (D1+), U1.10, U3.9 (TRD3+)
/CM4_GPIO ( Ethernet, GPIO, SDCARD)/TV_OUT: J2.11; also elsewhere on the board
/CM4_GPIO ( Ethernet, GPIO, SDCARD)/WL_nDis: J3.1, Module1.89 (WL_nDisable)
/CM4_GPIO ( Ethernet, GPIO, SDCARD)/nPWR_LED: Module1.95 (nPI_LED_PWR), U5.2
/CM4_GPIO ( Ethernet, GPIO, SDCARD)/nRPIBOOT: J2.2, Module1.93 (nRPIBOOT)
/RTC , Wakeup, FAN/SCL: Module1.80 (SCL0); also elsewhere on the board
/RTC , Wakeup, FAN/SDA: Module1.82 (SDA0); also elsewhere on the board
/nEXTRST: Module1.100 (nEXTRST); also elsewhere on the board
GND: C1.2, C5.2, J1.2, J2.1, J2.3, J2.7, J2.10, J2.12, J3.2, J7.6 (VSS), J7.11 (SHIELD), Module1.1 (GND), Module1.2 (GND), Module1.7 (GND), Module1.8 (GND), Module1.13 (GND), Module1.14 (GND), Module1.22 (GND), Module1.23 (GND), Module1.32 (GND), Module1.33 (GND), Module1.42 (GND), Module1.43 (GND), Module1.52 (GND), Module1.53 (GND), Module1.59 (GND), Module1.60 (GND), Module1.65 (GND), Module1.66 (GND), Module1.71 (GND), Module1.74 (GND), Module1.98 (GND), U1.3 (GND), U1.8 (GND), U2.3 (GND), U2.8 (GND), U3.19 (SHIELD), U3.20 (SHIELD), U5.3 (GND), U9.3 (GND), U18.2 (GND); also elsewhere on the board
unnamed: C1.1, U3.4 (CT), U3.5 (CT)
unnamed: D1.1 (K), R10.1, TP5.1
unnamed: D2.1 (K), R1.1, TP3.1
unnamed: J2.13, U9.4
unnamed: J7.10 (DET_A), R17.2
unnamed: J7.9 (DET_B), R18.2
unnamed: Module1.21 (PI_nLED_Activity), R1.2
unnamed: R10.2, U5.4
unnamed: R2.1, U3.16 (LEDG_K)
unnamed: R3.1, U3.18 (LEDY_K)

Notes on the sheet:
PWR LED
Ethernet POE Protection
CM4Lite SDCARD I/F
Ethernet
Activity LED
EEPROM write protect = Jumper Pins 3-4
Not Fitted headers
A button between pins 13-14 can be used to wake up compute module from power down
If compute modules is awake RUN_PG will be high so the button doesn't do anything If the compute module is asleep then RUN_PG will be at 0v and so pull global enable low
Force RPIBOOT = Jumper Pins 1-2
POE Header

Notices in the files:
kicad/CM4IO-KiCAD/CM4IOv5.kicad_sch:
© 2020-2022 Raspberry Pi Ltd (formerly Raspberry Pi (Trading) Ltd.)
